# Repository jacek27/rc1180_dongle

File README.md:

# rc1180_dongle

Used the library files from SnapEDA https://www.snapeda.com/

PCB for RadioCraft's RC1180-MBUS3 module with CH340C for usage with https://github.com/weetmuts/wmbusmeters

Trace for antena was calculated using https://www.pcbway.com/pcb_prototype/impedance_calculator.html

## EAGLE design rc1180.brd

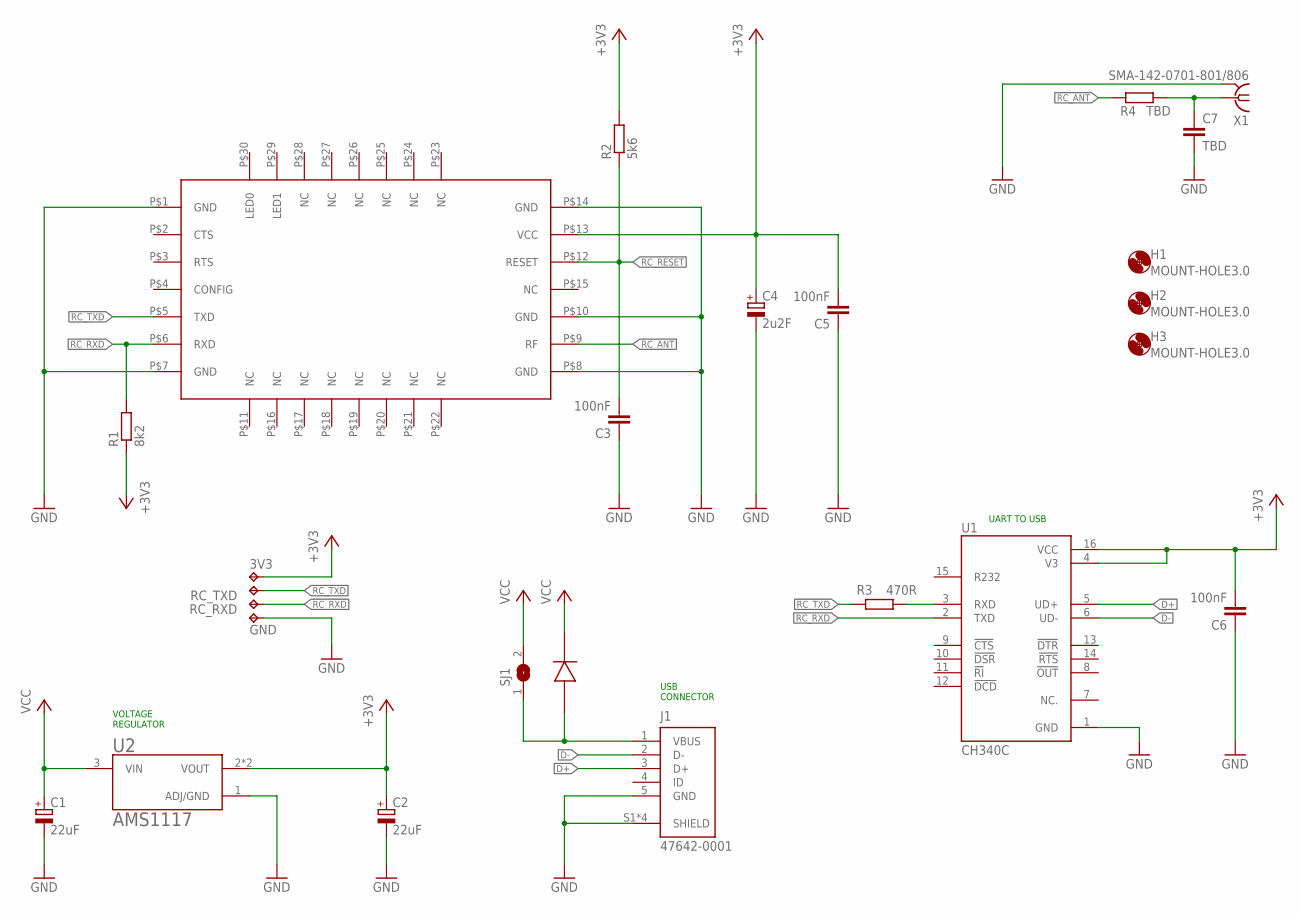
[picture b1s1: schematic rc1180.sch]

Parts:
3V3: TPB1,27; B1,27
C1, C2: 22uF; C/6032-28R
C3, C5, C6: 100nF; C0805K
C4: 2u2F; A/3216-18W
C7: TBD; C0603
GND: TPB1,27; B1,27
H1, H2, H3: MOUNT-HOLE3.0; 3,0
J1: 47642-0001; MOLEX_47642-0001
R1: 8k2; R0805
R2: 5k6; R0805
R3: 470R; R0805
R4: TBD; R0603
RC_RXD: TPB1,27; B1,27
RC_TXD: TPB1,27; B1,27
SJ1: SJ
U1: CH340C; SOIC127P600X180-16N
U2: AMS1117; SOT229P700X180-4N
U$1: RC1180-MBUS3
U$2: MBR0540; SOD123
X1: SMA-142-0701-801/806; J502-ND-142-0701-801/806

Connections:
+3V3: 3V3.TP, C2.+, C4.+, C5.2, C6.2, R1.1, R2.2, U1.4 (V3), U1.16 (VCC), U2.2 (VOUT), U2.4 (VOUT), U$1.P$13 (VCC)
D+: J1.3 (D+), U1.5 (UD+)
D-: J1.2 (D-), U1.6 (UD-)
GND: C1.-, C2.-, C3.1, C4.-, C5.1, C6.1, C7.2, GND.TP, J1.5 (GND), J1.S1 (SHIELD), J1.S2 (SHIELD), J1.S3 (SHIELD), J1.S4 (SHIELD), U1.1 (GND), U2.1 (ADJ/GND), U$1.P$1 (GND), U$1.P$7 (GND), U$1.P$8 (GND), U$1.P$10 (GND), U$1.P$14 (GND), X1.G@1 (2), X1.G@2 (2), X1.G@3 (2), X1.G@4 (2)
unnamed: R3.2, U1.3 (RXD)
unnamed: J1.1 (VBUS), SJ1.1, U$2.A
unnamed: C7.1, R4.2, X1.1
RC_ANT: R4.1, U$1.P$9 (RF)
RC_RESET: C3.2, R2.1, U$1.P$12 (RESET)
RC_RXD: R1.2, RC_RXD.TP, U1.2 (TXD), U$1.P$6 (RXD)
RC_TXD: R3.1, RC_TXD.TP, U$1.P$5 (TXD)
VCC: C1.+, SJ1.2, U2.3 (VIN), U$2.C (K)

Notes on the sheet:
USB CONNECTOR
VOLTAGE REGULATOR
UART TO USB

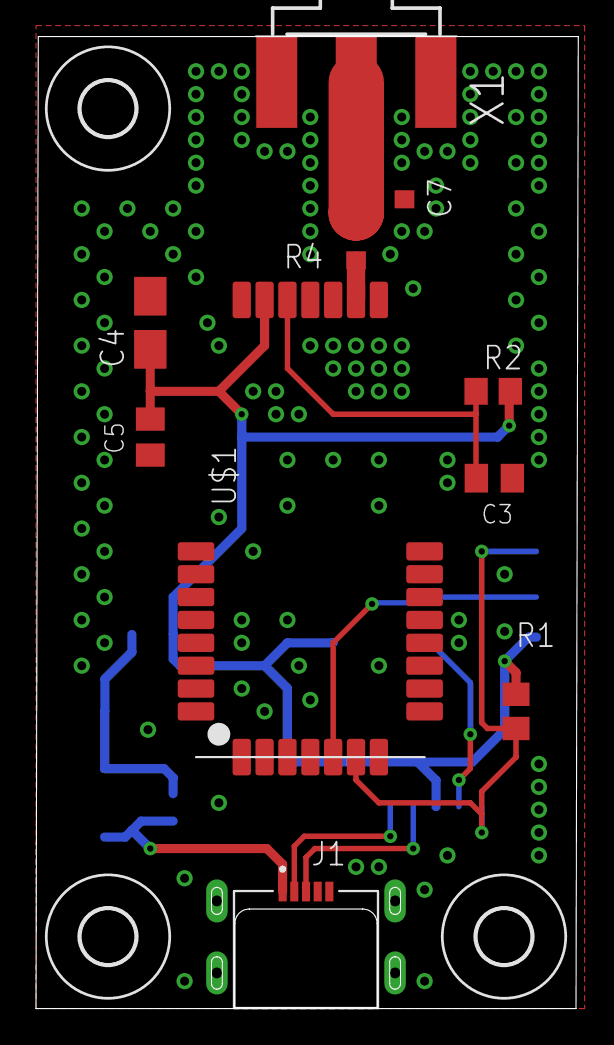
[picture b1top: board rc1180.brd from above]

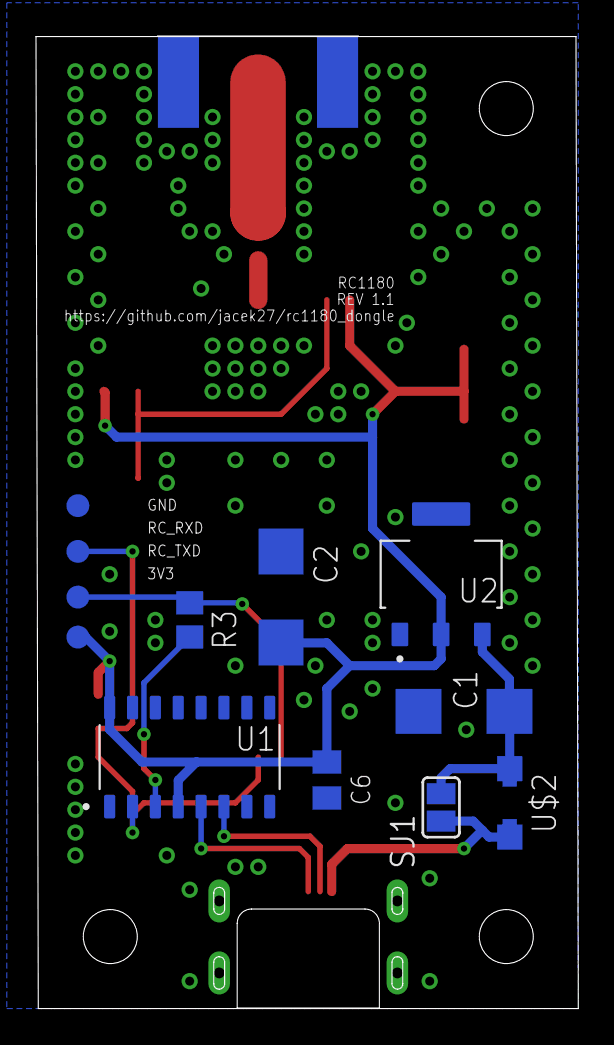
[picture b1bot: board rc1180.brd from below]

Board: 2 copper layers, 30.1 x 54.0 mm, 25 parts (12 on the bottom side), 12 nets.

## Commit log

2022-01-31 Add files via upload
    Added RC1180
2022-06-15 Added schematics and epf files
2022-06-17 Added lbr files from snapeda
2022-06-17 Updated lbrs
2022-06-17 Added ch340 and ams1117 vreg
2022-06-18 Added lbr for MBR0540
2022-06-18 Component placed / frame added
2022-06-18 Final touches
2022-06-18 First board commit
2022-06-18 Added holes and vias
2022-06-18 Added more vias and corrected component desc
2022-06-19 Added matching circuit for antenna
2022-06-21 Updated 100nF caps to be the same
2022-06-21 BOM based on Polish sources
2022-06-21 Extended board to 54 mm for easy soldering of rf connector
2022-06-21 Connected the 100nF updated cap
2022-06-21 Added rc1180_sch.pdf
2023-01-01 Added vias and testpoints
2023-01-01 Updated layer sets
2023-01-01 Added pdf prints
